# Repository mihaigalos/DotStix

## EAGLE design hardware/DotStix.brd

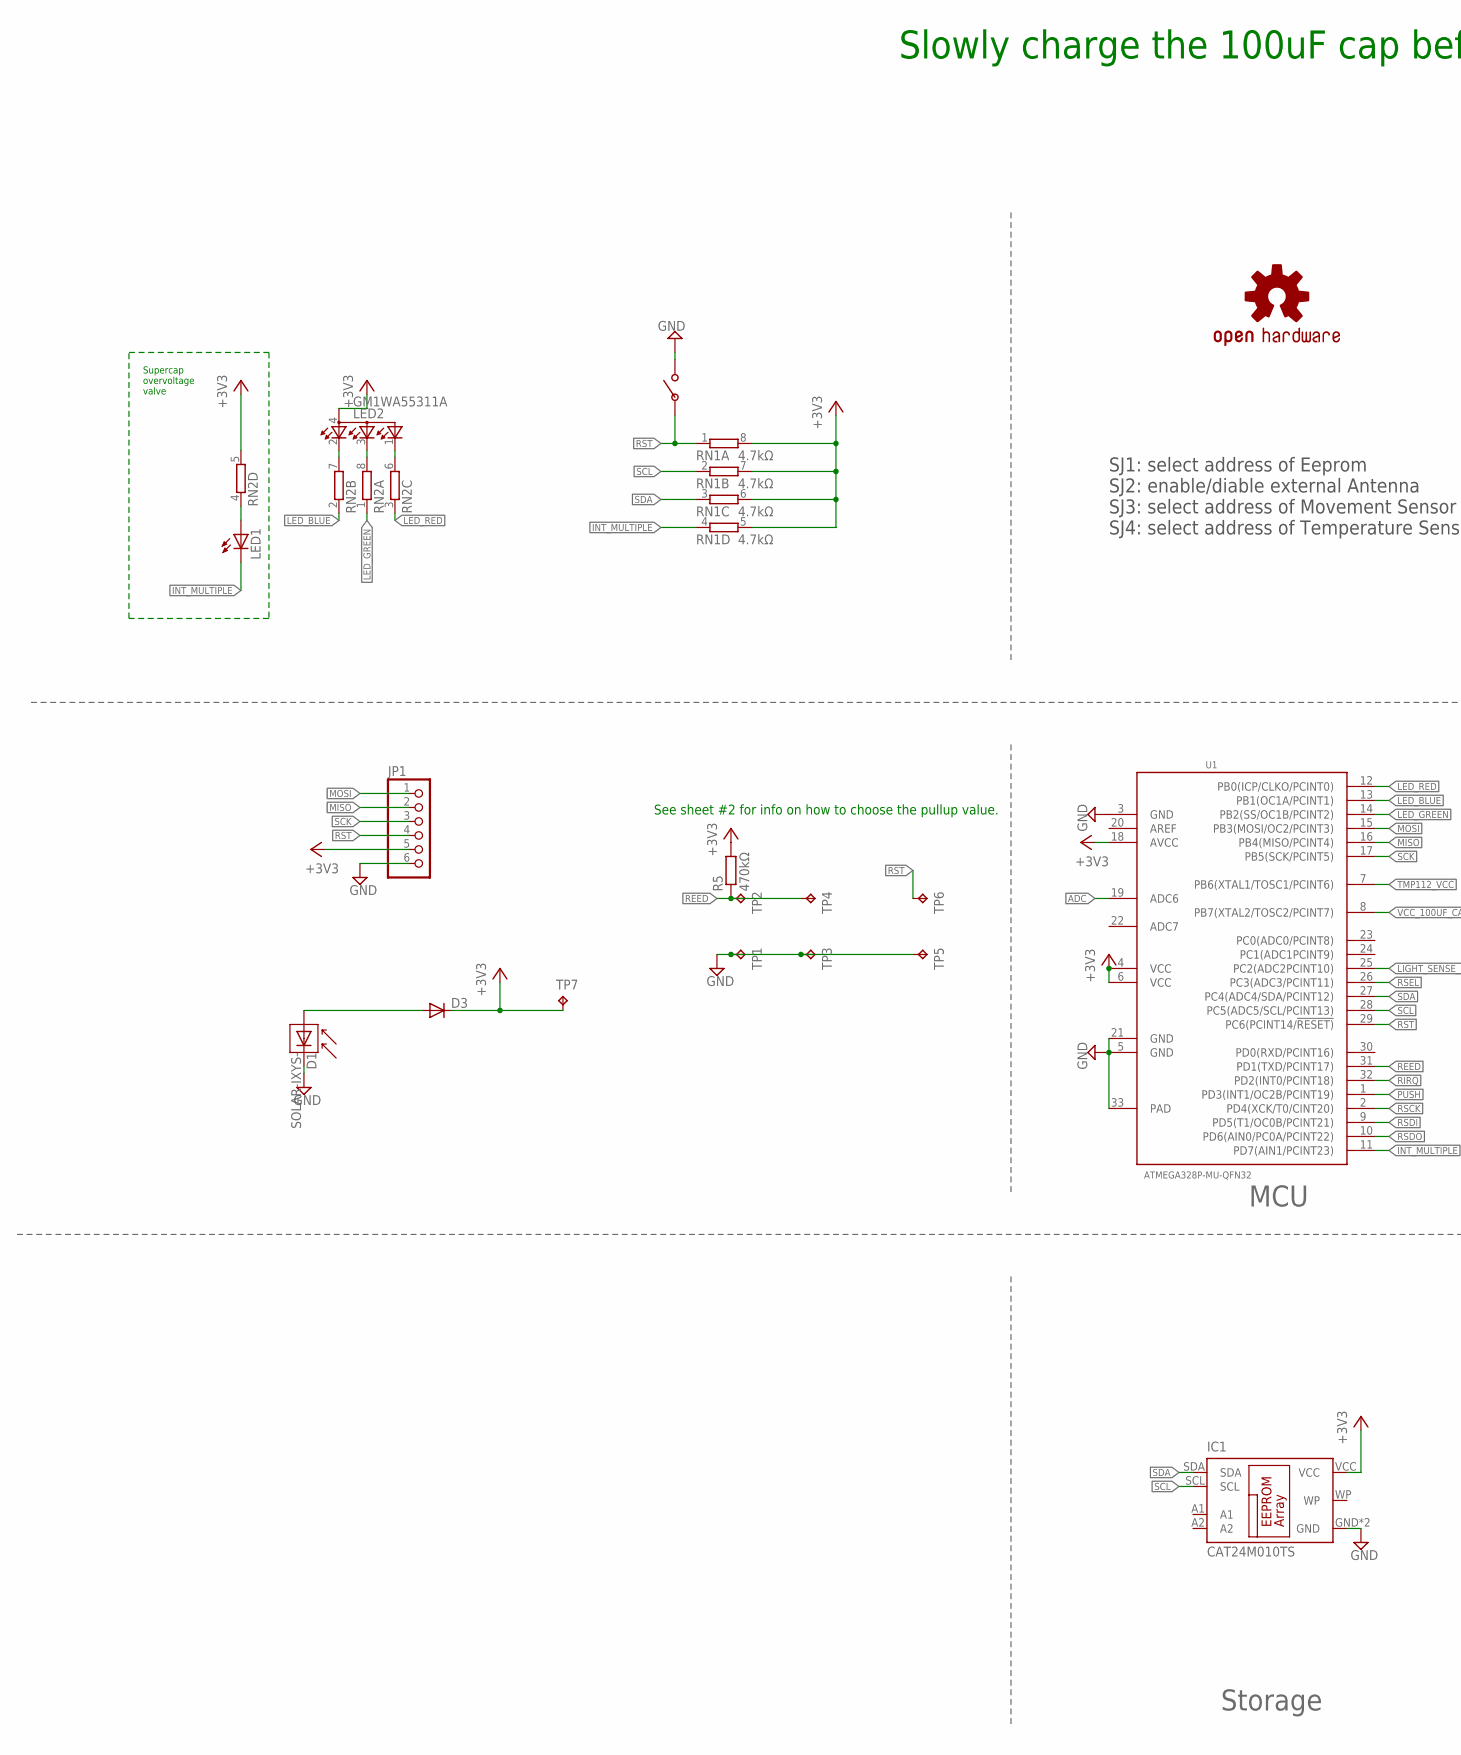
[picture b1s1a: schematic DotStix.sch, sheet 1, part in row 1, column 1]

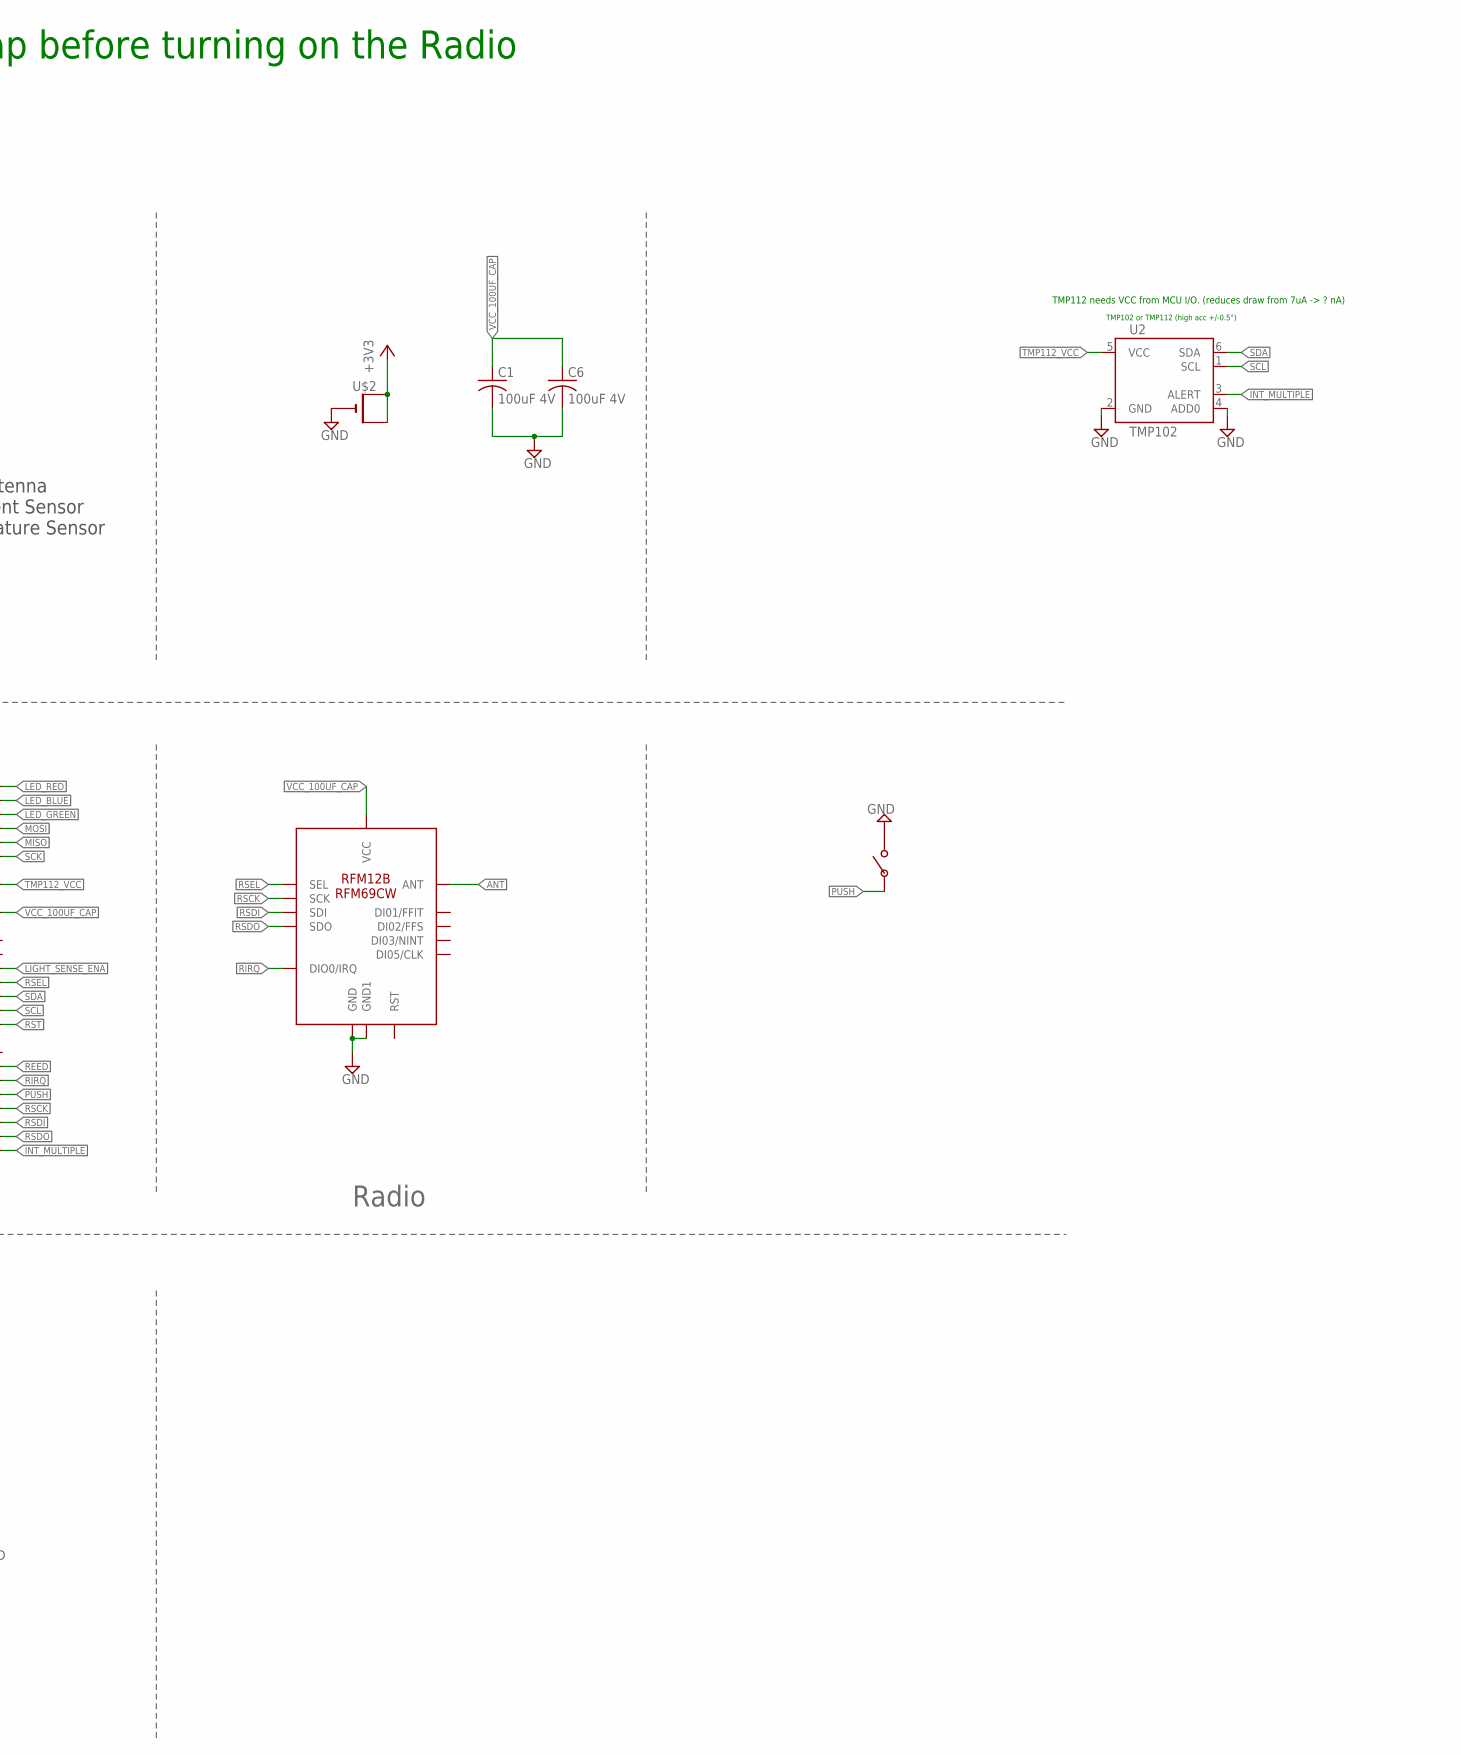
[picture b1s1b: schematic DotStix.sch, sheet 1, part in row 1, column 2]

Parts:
C1, C6: 100uF 4V; C3216
D1: SOLAR-IXYS-; SOLARBIT-12X1
D3: DIODE-SOD523; SOD523
IC1: CAT24M010TS; TSSOP8
JP1: PINHD-1X6; 1X06
LED1: LEDCHIP-LED0603; CHIP-LED0603
LED2: GM1WA55311A
LOGO1: OSHW-LOGOS; OSHW-LOGO-S
R5: 470kΩ; R0603
RN1: 4.7kΩ; 4X0402ARV341
RN2: 4R-N0402ARV341; 4X0402ARV341
TP1, TP2, TP3, TP4, TP5, TP6, TP7: TPTP20SQ; TP20SQ
U1: ATMEGA328P-MU-QFN32; QFN32G-0.5-5X5MM
U2: TMP102; SOT563
U$1: RFM12B/69CW
U$2: CR1220SMT; CR1220-SMD
U$3, U$4: PUSHBUTTON_4X2.5

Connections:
+3V3: D3.C, IC1.VCC, JP1.5, LED2.4 (A), R5.2, RN1.5 (2), RN1.6 (2), RN1.7 (2), RN1.8 (2), RN2.5 (2), TP7.TP, U1.4 (VCC), U1.6 (VCC), U1.18 (AVCC), U$2.+$1 (+), U$2.+$2 (+1)
ADC: U1.19 (ADC6)
ANT: U$1.ANT
GND: C1.2, C6.2, D1.- (C), IC1.GND, IC1.NC (GND), JP1.6, TP1.TP, TP3.TP, TP5.TP, U1.3 (GND), U1.5 (GND), U1.21 (GND), U1.33 (PAD), U2.2 (GND), U2.4 (ADD0), U$1.GND, U$1.GND1, U$2.-, U$3.P$2, U$4.P$2
INT_MULTIPLE: LED1.C, RN1.4 (1), U1.11 (PD7(AIN1/PCINT23)), U2.3 (ALERT)
LED_BLUE: RN2.2 (1), U1.13 (PB1(OC1A/PCINT1))
LED_GREEN: RN2.1, U1.14 (PB2(SS/OC1B/PCINT2))
LED_RED: RN2.3 (1), U1.12 (PB0(ICP/CLKO/PCINT0))
LIGHT_SENSE_ENA: U1.25 (PC2(ADC2PCINT10))
MISO: JP1.2, U1.16 (PB4(MISO/PCINT4))
MOSI: JP1.1, U1.15 (PB3(MOSI/OC2/PCINT3))
unnamed: LED2.2 (CRED), RN2.7 (2)
unnamed: D1.+ (A), D3.A
unnamed: LED2.3 (CBLUE), RN2.8 (2)
unnamed: LED2.1 (CGREEN), RN2.6 (2)
unnamed: LED1.A, RN2.4 (1)
PUSH: U1.1 (PD3(INT1/OC2B/PCINT19)), U$4.P$1
REED: R5.1, TP2.TP, TP4.TP, U1.31 (PD1(TXD/PCINT17))
RIRQ: U1.32 (PD2(INT0/PCINT18)), U$1.IRQ (DIO0/IRQ)
RSCK: U1.2 (PD4(XCK/T0/CINT20)), U$1.SCK
RSDI: U1.9 (PD5(T1/OC0B/PCINT21)), U$1.SDI
RSDO: U1.10 (PD6(AIN0/PC0A/PCINT22)), U$1.SDO
RSEL: U1.26 (PC3(ADC3/PCINT11)), U$1.SEL
RST: JP1.4, RN1.1, TP6.TP, U1.29 (PC6(PCINT14/!RESET)), U$3.P$1
SCK: JP1.3, U1.17 (PB5(SCK/PCINT5))
SCL: IC1.SCL, RN1.2 (1), U1.28 (PC5(ADC5/SCL/PCINT13)), U2.1 (SCL)
SDA: IC1.SDA, RN1.3 (1), U1.27 (PC4(ADC4/SDA/PCINT12)), U2.6 (SDA)
TMP112_VCC: U1.7 (PB6(XTAL1/TOSC1/PCINT6)), U2.5 (VCC)
VCC_100UF_CAP: C1.1, C6.1, U1.8 (PB7(XTAL2/TOSC2/PCINT7)), U$1.VDD (VCC)

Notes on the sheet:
SJ1: select address of Eeprom SJ2: enable/diable external Antenna SJ3: select address of Movement Sensor SJ4: select address of Temperature Sensor
MCU
Radio
See sheet #2 for info on how to choose the pullup value.
TMP102 or TMP112 (high acc +/-0.5°)
Storage
TMP112 needs VCC from MCU I/O. (reduces draw from 7uA -> ? nA)
Slowly charge the 100uF cap before turning on the Radio
Supercap overvoltage valve

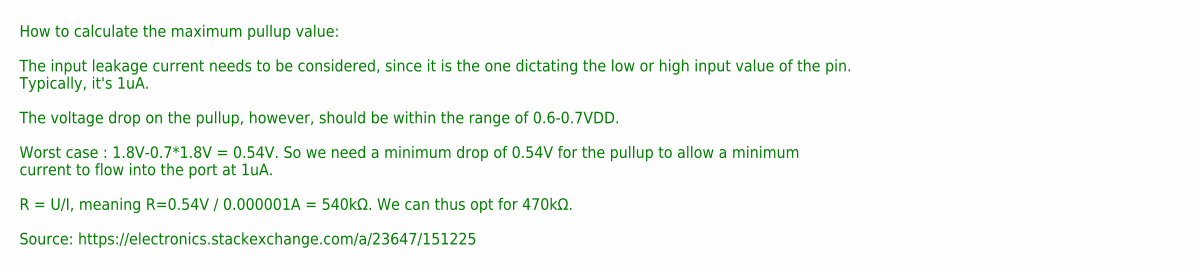
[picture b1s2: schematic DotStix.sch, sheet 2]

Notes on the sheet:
How to calculate the maximum pullup value: The input leakage current needs to be considered, since it is the one dictating the low or high input value of the pin. Typically, it's 1uA. The voltage drop on the pullup, however, should be within the range of 0.6-0.7VDD. Worst case : 1.8V-0.7*1.8V = 0.5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

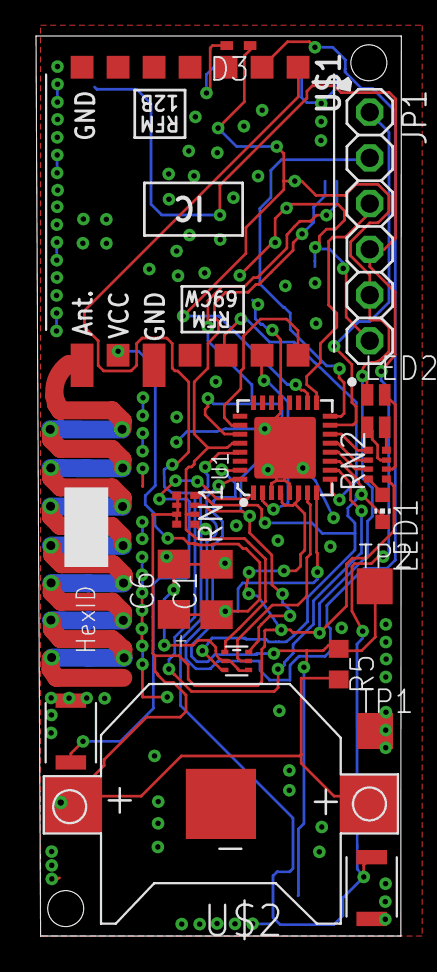
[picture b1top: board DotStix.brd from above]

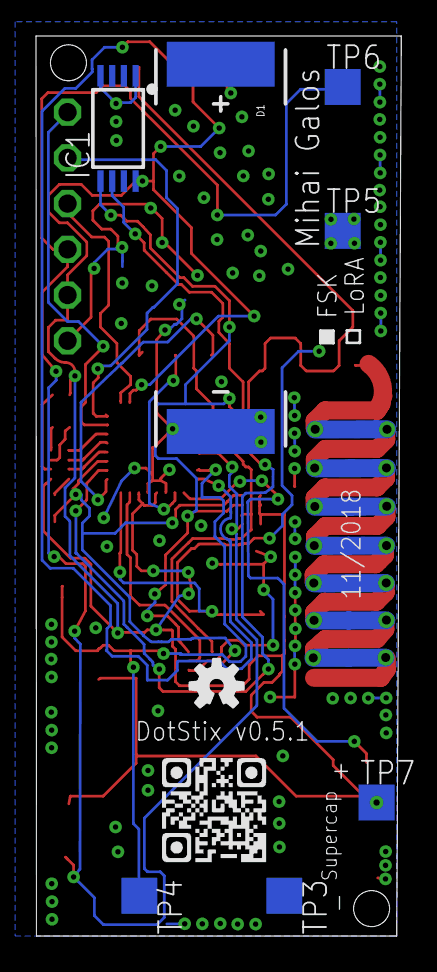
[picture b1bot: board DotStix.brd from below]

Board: 2 copper layers, 20.3 x 50.0 mm, 25 parts (8 on the bottom side), 26 nets.

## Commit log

2018-01-03 Add QR, labels, heavy GND, reposition battery
2018-01-03 Add reed switch
2018-01-03 Add polarity to 100uF cap
2018-01-03 Add key for MOSI, adjust R-array vias
2018-01-03 Add RST switch
2018-01-03 Major rework, add solar cell
2018-01-03 Add HexID, second reed on rear side
2018-01-03 Add photoresistor
2018-01-04 Minor info improvements
2018-01-04 Draft: Fix solar polarity, add 20ppm crystal
2018-01-04 Fix solar polarity, add 20ppm crystal
2018-01-04 Update version info
2018-01-04 Rearrange pin connections around MCU
2018-01-04 Readjust vias
2018-01-04 Add battery polarity logos
2018-01-05 Add weak pullup for low current with battery
2018-01-05 Add 100uF cap
2018-01-06 Exp: Add Temp & UV sensors
2018-01-06 Add via restrict to corners of MCU
2018-01-06 Draft : first routing
2018-01-06 Finished integration of Temp and UV sensors
2018-01-06 Move fast signals away from underneath XTAL
2018-01-06 Fix unconnected 4.7k pullups
2018-01-06 Draft: add 9DoF motion sensor
2018-01-06 Draft: 9DoF pins connected, need to fix warnings
2018-01-06 Add 9Dof: removed warnings
2018-01-06 Move solar panel further away from UV sensor
2018-01-06 Adjust author name position
2018-01-07 Add 256kb EEPROM
2018-01-16 Add reed switch for RST. Required for potting
2018-01-16 Increment version, rearrange text
2018-01-31 Modify pullup value for reed, add explanation
2018-01-31 Remove unnecessary solder jumper
2018-02-08 Move 3V3 Zener to low side of Schottky
2018-09-30 Add infos to minimize power
2018-09-30 Add NMOS to minimize leakage through 100uF cap
2018-09-30 Cleanup unused, improve GND
2018-09-30 Increase version
2018-09-30 Update version, remove superfluous doc
2018-09-30 Remove NMOSFET, connect 100uF to IO directly
2018-10-18 Led on INT_MULTIPLE, tStop for Supercap GND
2018-10-18 Update descriptions
2018-10-18 Move tStop downstream from battery holder
2018-10-18 Add second 100uF cap for RF
2018-10-19 Duplicate battery pads to tBottom for supercap
2019-07-21 Correct supercap pad, add labels for radio & supercap
2019-07-21 Shift supercap pad to exterior

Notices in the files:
parts and their libraries:
Particle-Devices: Licensing: Designed by Particle.
SparkFun: Licensing: CC v3.0 Share-Alike You are welcome to use this library for commercial purposes.
